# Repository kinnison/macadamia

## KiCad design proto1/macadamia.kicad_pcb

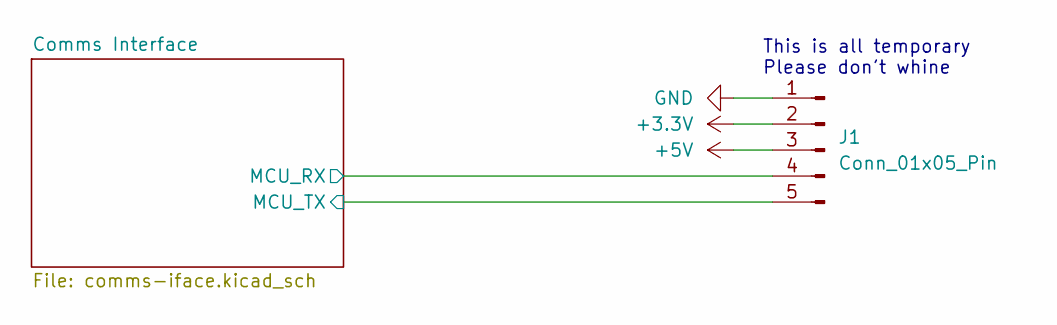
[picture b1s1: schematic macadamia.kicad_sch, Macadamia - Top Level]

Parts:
J1: Conn_01x05_Pin; PinHeader_1x05_P2.54mm_Vertical

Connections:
+3.3V: J1.2; also elsewhere on the board
+5V: J1.3; also elsewhere on the board
/Comms Interface/MCU_RX: J1.4; also elsewhere on the board
/Comms Interface/MCU_TX: J1.5; also elsewhere on the board
GND: J1.1; also elsewhere on the board

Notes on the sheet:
This is all temporary Please don't whine

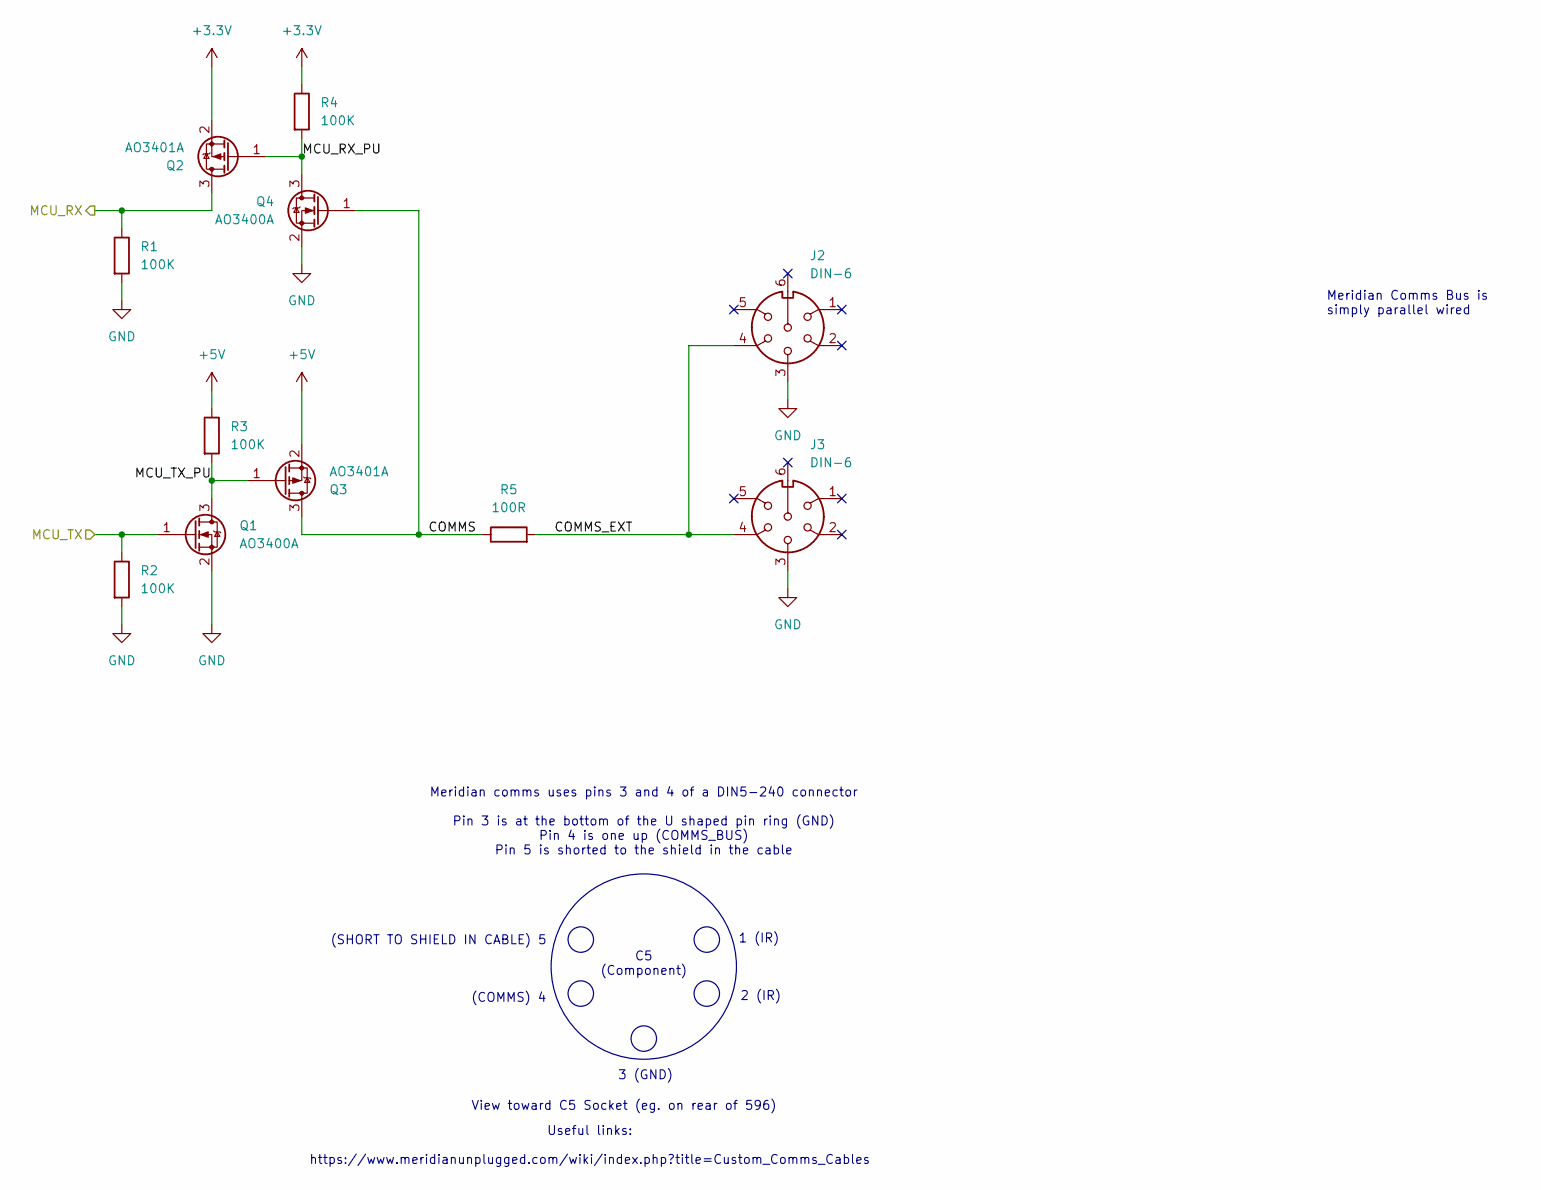
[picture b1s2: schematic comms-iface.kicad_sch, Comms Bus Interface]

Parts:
J2, J3: DIN-6; DIN-45322-010599-06
Q1, Q4: AO3400A; SOT-23-3; JLCPCB Part # C20917
Q2, Q3: AO3401A; SOT-23-3; JLCPCB Part # C15127
R1, R2, R3, R4: 100K; R_0603_1608Metric; JLCPCB Part # C25803
R5: 100R; R_0603_1608Metric; JLCPCB Part # C22775

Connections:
+3.3V: Q2.2 (S), R4.1; also elsewhere on the board
+5V: Q3.2 (S), R3.1; also elsewhere on the board
/Comms Interface/COMMS: Q3.3 (D), Q4.1 (G), R5.1
/Comms Interface/COMMS_EXT: J2.4, J3.4, R5.2
/Comms Interface/MCU_RX: Q2.3 (D), R1.1; also elsewhere on the board
/Comms Interface/MCU_RX_PU: Q2.1 (G), Q4.3 (D), R4.2
/Comms Interface/MCU_TX: Q1.1 (G), R2.1; also elsewhere on the board
/Comms Interface/MCU_TX_PU: Q1.3 (D), Q3.1 (G), R3.2
GND: J2.3, J3.3, Q1.2 (S), Q4.2 (S), R1.2, R2.2; also elsewhere on the board

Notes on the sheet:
3 (GND)
Useful links: https://www.meridianunplugged.com/wiki/index.php?title=Custom_Comms_Cables
(SHORT TO SHIELD IN CABLE) 5
1 (IR)
(COMMS) 4
Meridian Comms Bus is simply parallel wired
2 (IR)
View toward C5 Socket (eg. on rear of 596)
Meridian comms uses pins 3 and 4 of a DIN5-240 connector Pin 3 is at the bottom of the U shaped pin ring (GND) Pin 4 is one up (COMMS_BUS) Pin 5 is shorted to the shield in the cable
C5 (Component)

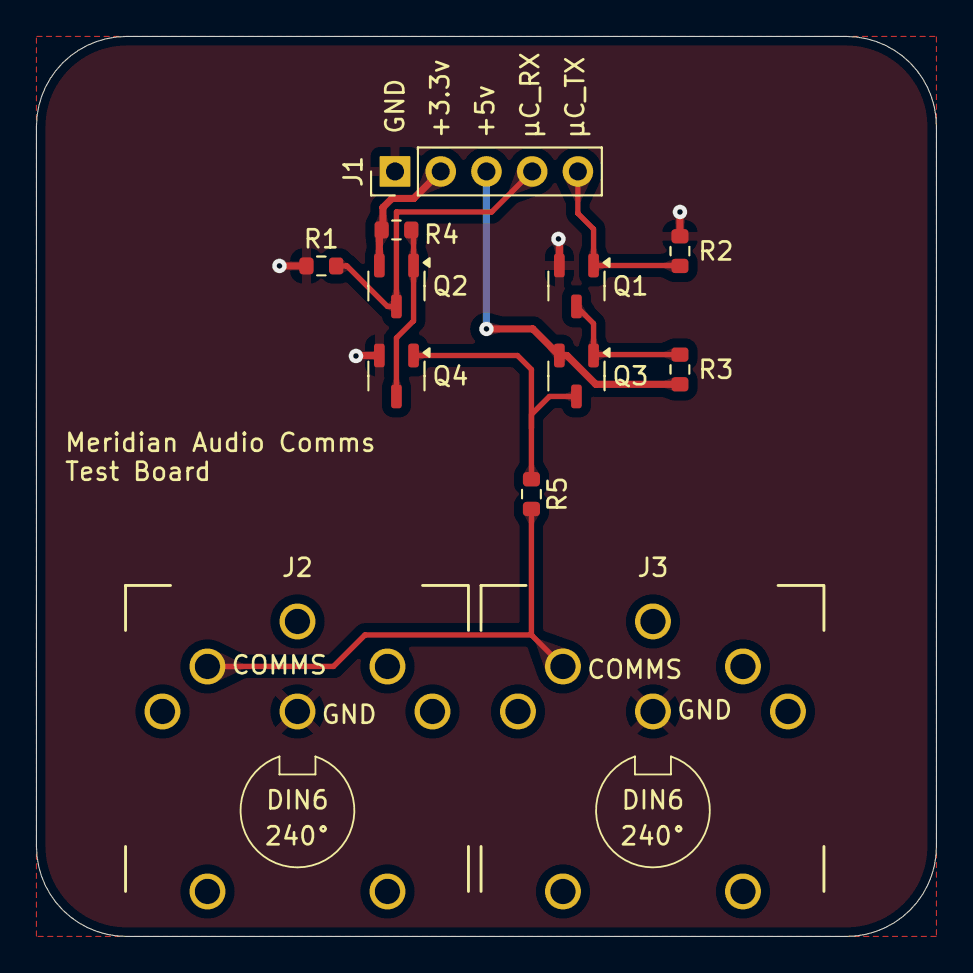
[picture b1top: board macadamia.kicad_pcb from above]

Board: 2 copper layers, 50.0 x 50.0 mm, 12 parts (0 on the bottom side), 9 nets.

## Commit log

2025-01-01 chore: Initial stuff before I begin
2025-01-01 proto1: Close to done
2025-01-03 proto1-code: Framework, not building yet
2025-01-03 chore: Add nix direnv
2025-01-03 proto1-code: Trivial latency measurer
2025-01-03 proto1-code: Bring CPU up to 48MHz
2025-01-03 proto1: Fix pfet orientation
2025-01-03 proto1-code: Improve latency measure precision
2025-01-03 proto1-code: Theoretically ready to receive packets
